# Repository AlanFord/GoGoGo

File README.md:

# GoGoGo
These projects support the GoGoGo module of the Contextual Electronics course.

The MotorDrive is a circuit board design that supports a brushed DC motor driver.

The EncoderBoard is a circuit board design that supports an optical motor encoder suitable for use with an encoder wheel (see below).

The EncoderWheel is the design for an encoder wheel that will fit the Sparkfun Shadow chasis (ROB-13301) and a Sparkfun 140 RPM hobby gearmotor (ROB-13302).

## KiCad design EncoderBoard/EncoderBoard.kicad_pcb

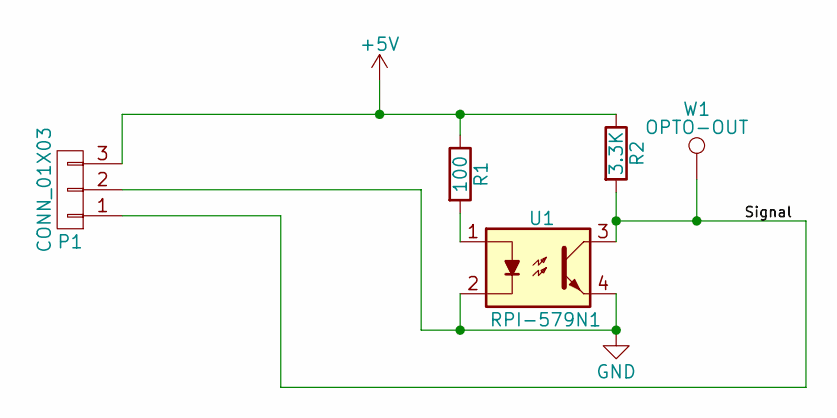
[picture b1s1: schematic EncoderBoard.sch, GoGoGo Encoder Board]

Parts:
P1: CONN_01X03; Pin_Header_Angled_1x03
R1: 100; R_0805_HandSoldering
R2: 3.3K; R_0805_HandSoldering
U1: RPI-579N1
W1: OPTO-OUT; Measurement_Point_Square-SMD-Pad_Big

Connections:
+5V: P1.3, R1.1, R2.1
/Signal: P1.1, R2.2, U1.3, W1.1
GND: P1.2, U1.2, U1.4
unnamed: R1.2, U1.1

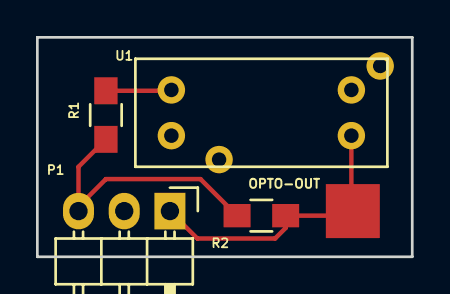
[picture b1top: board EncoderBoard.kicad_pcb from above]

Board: 2 copper layers, 20.8 x 12.2 mm, 5 parts (0 on the bottom side), 4 nets.

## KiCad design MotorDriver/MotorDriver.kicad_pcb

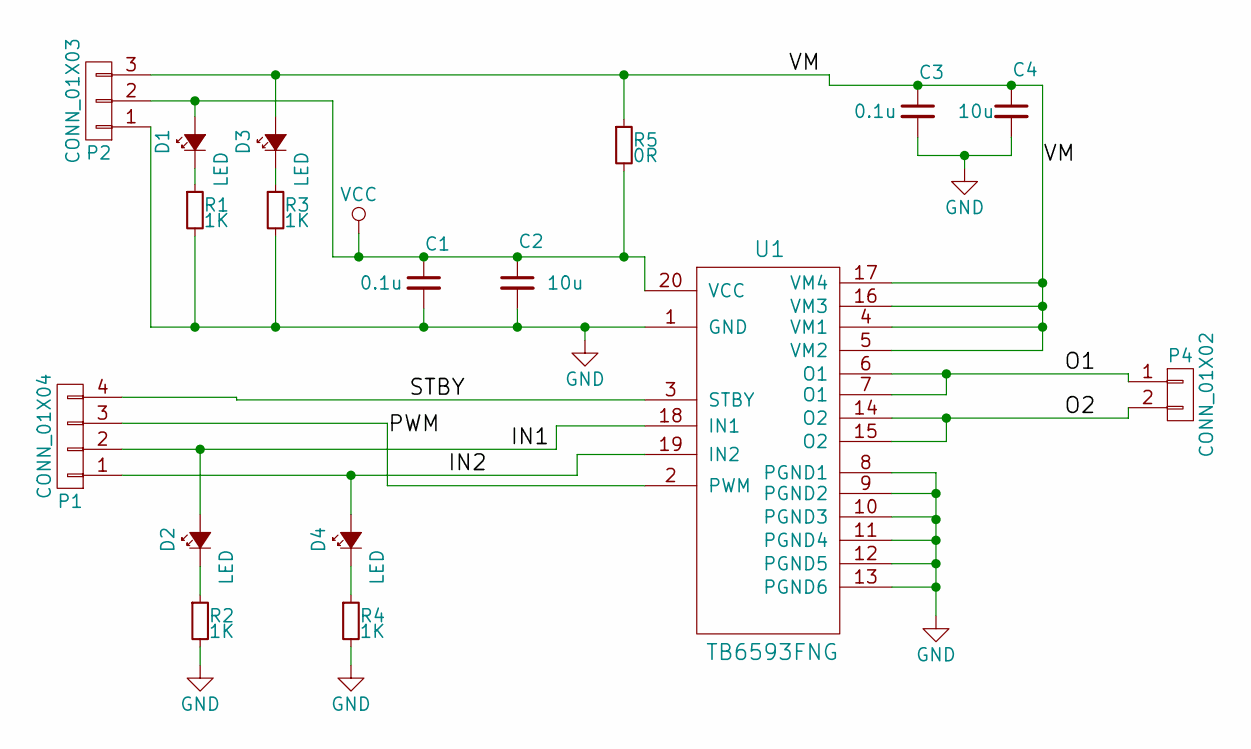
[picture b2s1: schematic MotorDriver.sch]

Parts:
C1, C3: 0.1u; C_0805
C2, C4: 10u; C_1206_HandSoldering
D1, D2, D3, D4: LED; LED_0805
P1: CONN_01X04; Pin_Header_Straight_1x04
P2: CONN_01X03; Pin_Header_Straight_1x03
P4: CONN_01X02; Pin_Header_Straight_1x02
R1, R2, R3, R4: 1K; R_0805_HandSoldering
R5: 0R; R_0805
U1: TB6593FNG; SSOP-20

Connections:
/IN1: D2.2 (A), P1.2, U1.18 (IN1)
/IN2: D4.2 (A), P1.1, U1.19 (IN2)
/O1: P4.1, U1.6 (O1), U1.7 (O1)
/O2: P4.2, U1.14 (O2), U1.15 (O2)
/PWM: P1.3, U1.2 (PWM)
/STBY: P1.4, U1.3 (STBY)
/VM: C3.1, C4.1, D3.2 (A), P2.3, R5.1, U1.4 (VM1), U1.5 (VM2), U1.16 (VM3), U1.17 (VM4)
GND: C1.2, C2.2, C3.2, C4.2, P2.1, R1.2, R2.2, R3.2, R4.2, U1.1 (GND), U1.8 (PGND1), U1.9 (PGND2), U1.10 (PGND3), U1.11 (PGND4), U1.12 (PGND5), U1.13 (PGND6)
unnamed: D1.1 (K), R1.1
unnamed: D2.1 (K), R2.1
unnamed: D3.1 (K), R3.1
unnamed: D4.1 (K), R4.1
VCC: C1.1, C2.1, D1.2 (A), P2.2, R5.2, U1.20 (VCC)

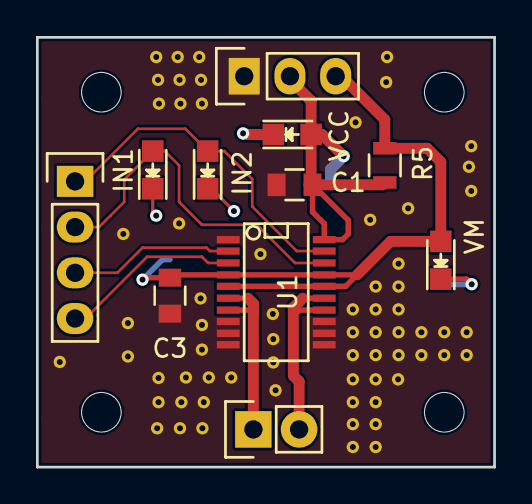
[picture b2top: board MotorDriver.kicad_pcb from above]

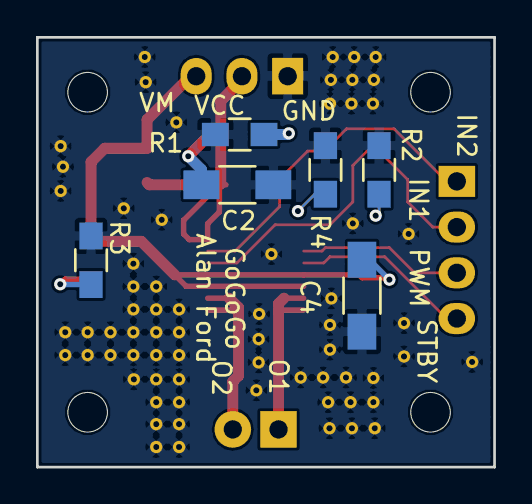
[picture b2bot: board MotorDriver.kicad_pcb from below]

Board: 2 copper layers, 25.4 x 23.9 mm, 17 parts (6 on the bottom side), 13 nets.

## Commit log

2016-12-24 added a README.md project discription
2016-12-24 added encode wheel design objectives
2016-12-24 updaed encoder wheel dimensions
2016-12-25 added encoder wheel measurements and initialized KiCad files
2016-12-26 first attempt at pcb layout
2016-12-28 generate gerbers
2017-01-15 initial motor driver board layout and traces
2017-01-18 finished motor driver layout and generated gerbers
2017-01-18 adjusted soldermask and updated gerbers
2017-01-18 zipped gerbers
2017-02-09 changed the pull up resistor to 3.3K
2017-02-09 initial design of encoder wheel for laser cutter and gcode for Othermill
2017-02-09 restored README.md
